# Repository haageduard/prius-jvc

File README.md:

# JVC KD-XT50BT remote control for Toyota Prius NHW20

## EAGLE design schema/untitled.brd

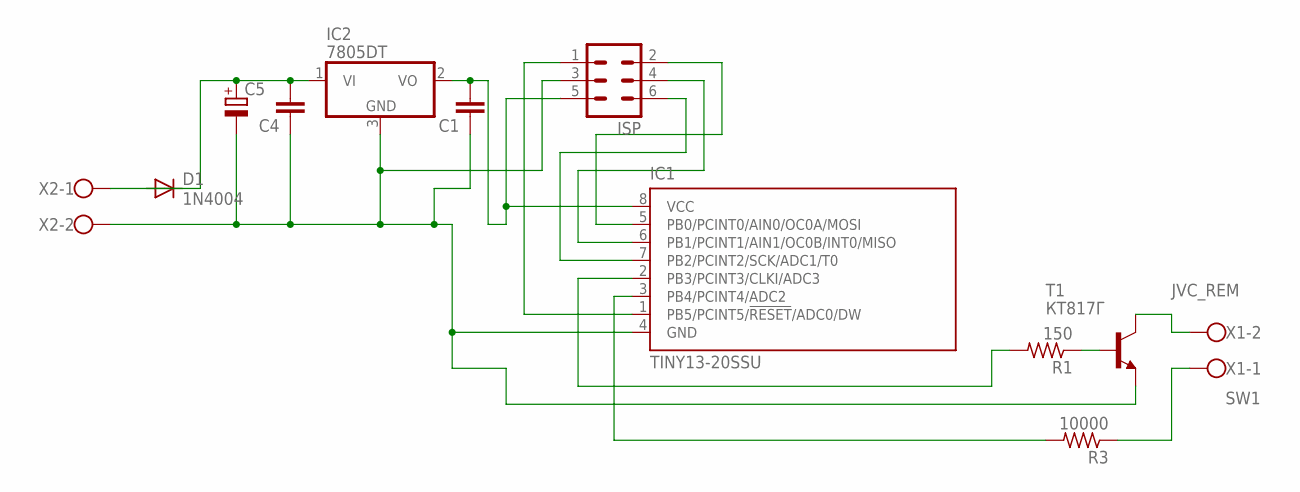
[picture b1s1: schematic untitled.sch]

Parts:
C1, C4: C2.5/2; C2.5-2
C5: CPOL-EUE5-10.5; E5-10,5
D1: 1N4004; DO41-10
IC1: TINY13-20SSU; 8S1
IC2: 7805DT; TO252
ISP: MA03-2
R1: 150; M1206
R3: 10000; M1206
T1: КТ817Г; TO220AV
X1, X2: W237-102

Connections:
JVC_REM: T1.2 (C), X1.2
unnamed: IC1.2 (PB3/PCINT3/CLKI/ADC3), R1.2
unnamed: C4.2, C5.+, D1.A, IC2.1 (VI)
unnamed: IC1.6 (PB1/PCINT1/AIN1/OC0B/INT0/MISO), ISP.4
unnamed: C1.1, C4.1, C5.-, IC1.4 (GND), IC2.3 (GND), ISP.3, T1.3 (E), X2.2
unnamed: R1.1, T1.1 (B)
unnamed: IC1.7 (PB2/PCINT2/SCK/ADC1/T0), ISP.6
unnamed: D1.C, X2.1
unnamed: IC1.5 (PB0/PCINT0/AIN0/OC0A/MOSI), ISP.2
unnamed: IC1.3 (PB4/PCINT4/ADC2), R3.2
unnamed: IC1.1 (PB5/PCINT5/!RESET!/ADC0/DW), ISP.1
unnamed: C1.2, IC1.8 (VCC), IC2.2 (VO), ISP.5
SW1: R3.1, X1.1

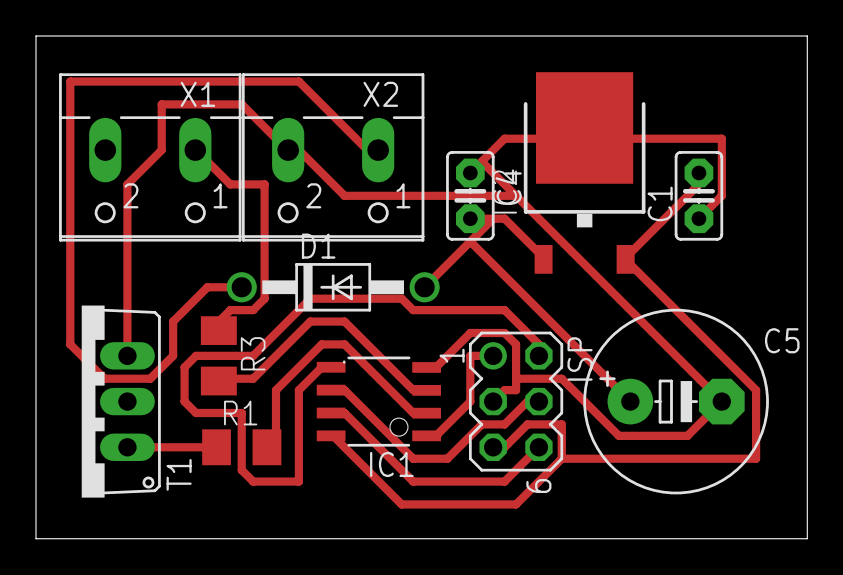
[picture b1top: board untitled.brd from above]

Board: 2 copper layers, 42.9 x 27.9 mm, 12 parts (0 on the bottom side), 13 nets.

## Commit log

2017-09-21 schema added comment refactoring
2017-09-21 added README.md
